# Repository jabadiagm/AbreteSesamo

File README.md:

# Ábrete Sésamo
Detector de proximidad / apertura de puertas por bluetooth

Ábrete Sésamo es un detector de proximidad basado en bluetooth que permite abrir la puerta de un hogar o de un garaje al detectar un dispositivo bluetooth dentro de un rango de 10m, aproximadamente. La centralita está formada por un arduino mega y una placa auxiliar. La placa contiene un relé para conectar al circuito de apertura y tres chips de bluetooth (2xHC05 + BLE112). El primer HC05 sirve para detectar teléfonos anteriores a los smartphones. El segundo HC05 detecta smartphones con bluetooth 1-3. Y el BLE112 sirve para smartphones con bluetooth 4. Los smartphones deben incluir una aplicación que se comunique con la centralita.

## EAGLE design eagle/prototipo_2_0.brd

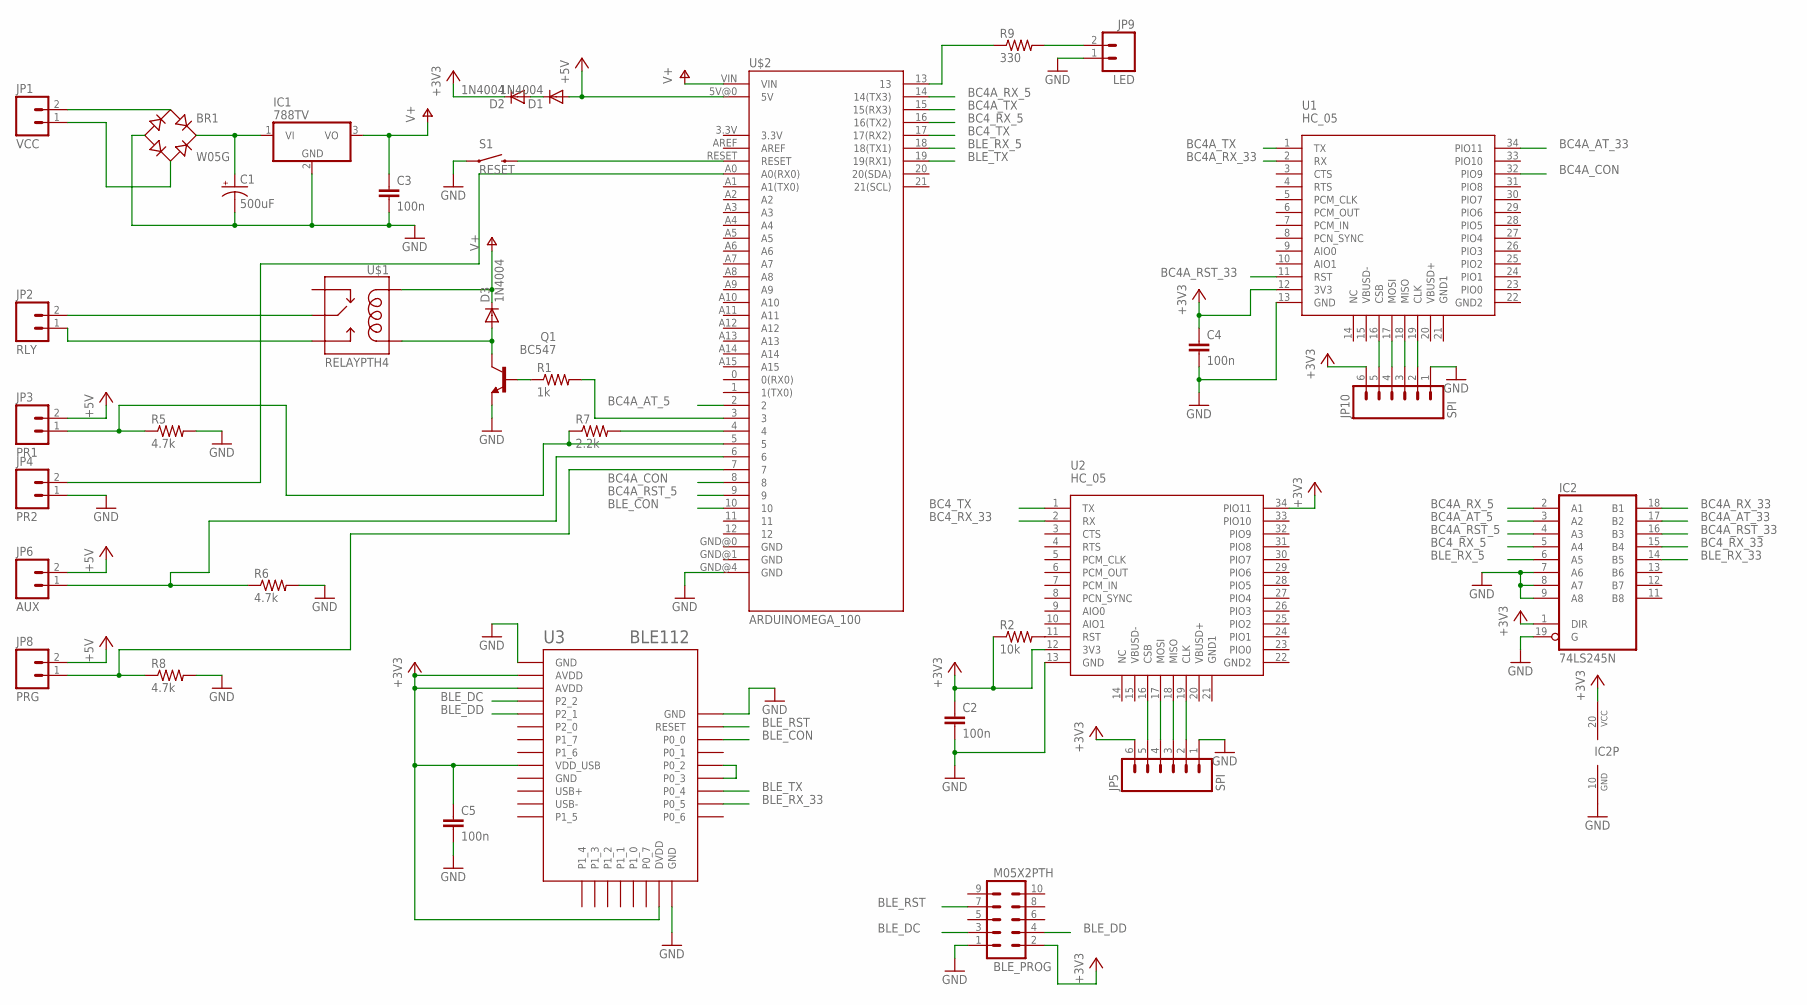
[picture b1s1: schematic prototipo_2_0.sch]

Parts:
BLE_PROG: M05X2PTH; AVR_ICSP
BR1: W05G; WOG
C1: 500uF; CPOL-RADIAL-1000UF-25V
C2, C3, C4, C5: 100n; C5B3
D1, D2, D3: 1N4004; DO41-10
IC1: 788TV; TO220V
IC2: 74LS245N; DIL20
JP1: VCC; SCREWTERMINAL-3.5MM-2
JP2: RLY; SCREWTERMINAL-3.5MM-2
JP3: PR1; SCREWTERMINAL-3.5MM-2
JP4: PR2; SCREWTERMINAL-3.5MM-2
JP5, JP10: SPI; 1X06
JP6: AUX; SCREWTERMINAL-3.5MM-2
JP8: PRG; SCREWTERMINAL-3.5MM-2
JP9: LED; SCREWTERMINAL-3.5MM-2
Q1: BC547; TO92
R1: 1k; AXIAL-0.4
R2: 10k; AXIAL-0.4
R5, R6, R8: 4.7k; AXIAL-0.4
R7: 2.2k; AXIAL-0.4
R9: 330; AXIAL-0.4
S1: RESET; TACTILE_SWITCH_SMD
U1, U2: HC_05; BLUETOOTH_SMD
U3: BLE112; BLE112-A
U$1: RELAYPTH4; RELAY-JZC
U$2: ARDUINOMEGA_100

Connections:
+3V3: BLE_PROG.2, C2.1, C4.1, C5.1, D2.C, IC2.1 (DIR), IC2.20 (VCC), JP5.6, JP10.6, R2.P$1 (1), U1.12 (3V3), U2.12 (3V3), U2.34 (PIO11), U3.AVDD1 (AVDD), U3.AVDD2 (AVDD), U3.DVDD, U3.VDD_USB
+5V: D1.A, JP3.2, JP6.2, JP8.2, U$2.5V@0 (5V)
BC4A_AT_5: IC2.3 (A2), U$2.2
BC4A_AT_33: IC2.17 (B2), U1.34 (PIO11)
BC4A_CON: U1.32 (PIO9), U$2.8
BC4A_RST_5: IC2.4 (A3), U$2.9
BC4A_RST_33: IC2.16 (B3), U1.11 (RST)
BC4A_RX_5: IC2.2 (A1), U$2.14 (14(TX3))
BC4A_RX_33: IC2.18 (B1), U1.2 (RX)
BC4A_TX: U1.1 (TX), U$2.15 (15(RX3))
BC4_RX_5: IC2.5 (A4), U$2.16 (16(TX2))
BC4_RX_33: IC2.15 (B4), U2.2 (RX)
BC4_TX: U2.1 (TX), U$2.17 (17(RX2))
BLE_CON: U3.P0_0, U$2.10
BLE_DC: BLE_PROG.3, U3.P2_2
BLE_DD: BLE_PROG.4, U3.P2_1
BLE_RST: BLE_PROG.7, U3.RESET
BLE_RX_5: IC2.6 (A5), U$2.18 (18(TX1))
BLE_RX_33: IC2.14 (B5), U3.P0_5
BLE_TX: U3.P0_4, U$2.19 (19(RX1))
GND: BLE_PROG.1, BR1.-, C1.2 (-), C2.2, C3.2, C4.2, C5.2, IC1.2 (GND), IC2.7 (A6), IC2.8 (A7), IC2.9 (A8), IC2.10 (GND), IC2.19 (G), JP4.1, JP5.1, JP9.1, JP10.1, Q1.1 (E), R5.P$2 (2), R6.P$2 (2), R8.P$2 (2), S1.1, U1.13 (GND), U2.13 (GND), U3.GND1 (GND), U3.GND2 (GND), U3.GND3 (GND), U3.GND4 (GND), U$2.GND@4 (GND)
unnamed: R2.P$2 (2), U2.11 (RST)
unnamed: D1.C, D2.A
unnamed: BR1.+, C1.1 (+), IC1.1 (VI)
unnamed: R1.P$2 (2), U$2.3
unnamed: Q1.2 (B), R1.P$1 (1)
unnamed: D3.A, Q1.3 (C), U$1.1 (COIL2)
unnamed: JP2.1, U$1.3 (NO)
unnamed: JP2.2, U$1.4 (MAIN)
unnamed: S1.3 (2), U$2.RESET
unnamed: U3.P0_2, U3.P0_3
unnamed: JP5.2, U2.19 (CLK)
unnamed: JP5.3, U2.18 (MISO)
unnamed: JP5.4, U2.17 (MOSI)
unnamed: JP5.5, U2.16 (CSB)
unnamed: JP10.5, U1.16 (CSB)
unnamed: JP3.1, R5.P$1 (1), R7.P$1 (1), U$2.5
unnamed: JP6.1, R6.P$1 (1), U$2.6
unnamed: R7.P$2 (2), U$2.4
unnamed: JP8.1, R8.P$1 (1), U$2.7
unnamed: JP10.4, U1.17 (MOSI)
unnamed: R9.P$1 (1), U$2.13
unnamed: JP9.2, R9.P$2 (2)
unnamed: JP10.3, U1.18 (MISO)
unnamed: JP10.2, U1.19 (CLK)
unnamed: JP4.2, U$2.A0 (A0(RX0))
V+: C3.1, D3.C, IC1.3 (VO), U$1.5 (COIL1), U$2.VIN
VCC1: BR1.AC1, JP1.2
VCC2: BR1.AC2, JP1.1

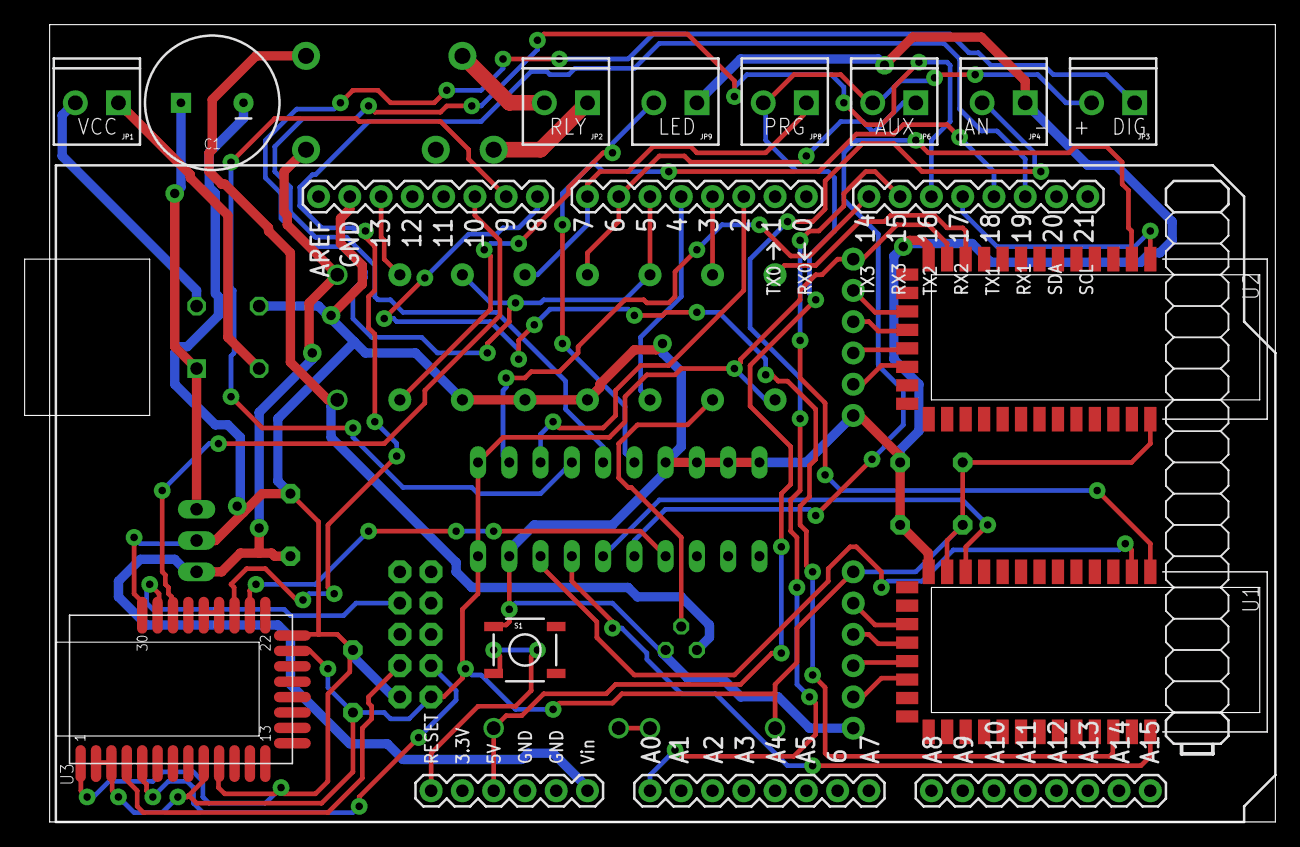
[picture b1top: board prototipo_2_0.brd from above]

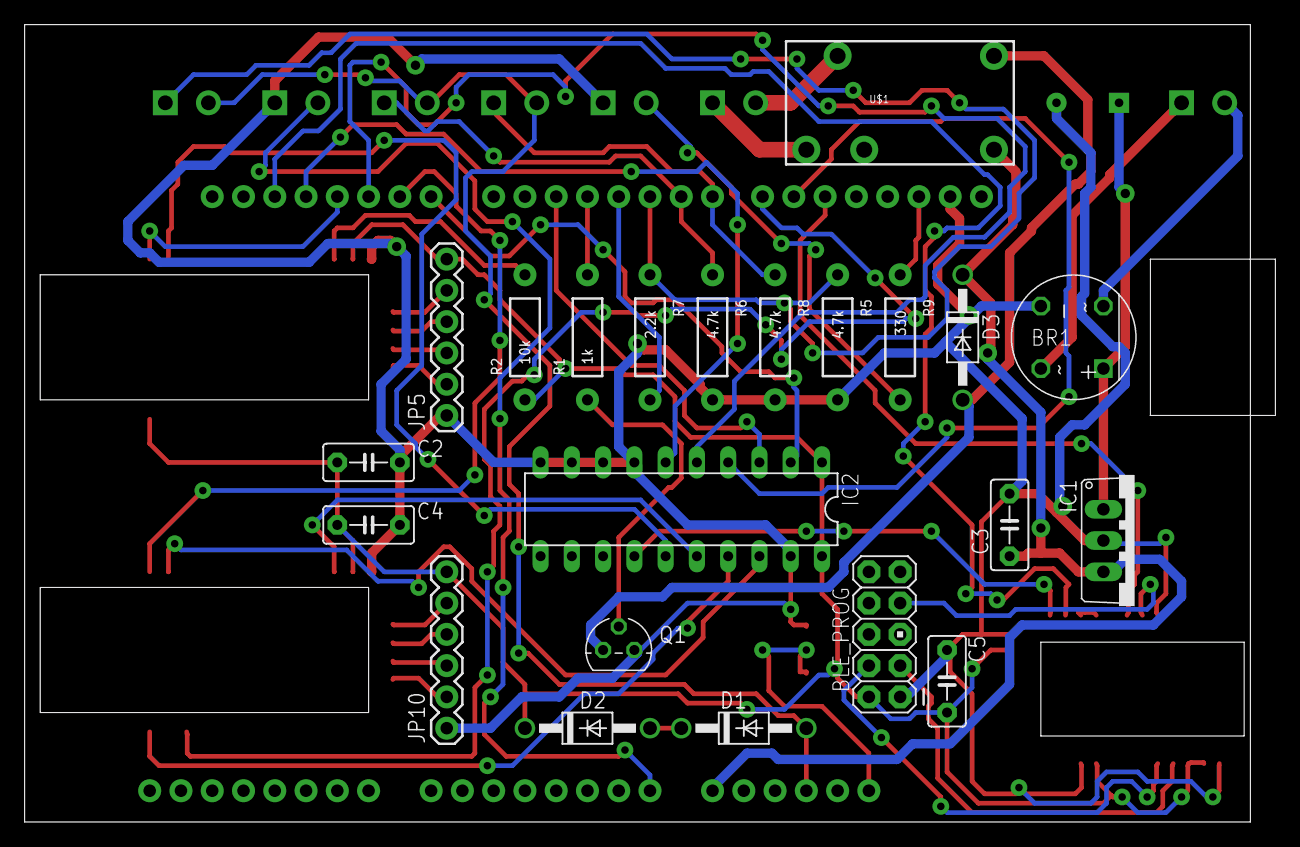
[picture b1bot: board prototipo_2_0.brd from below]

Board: 2 copper layers, 101.6 x 64.8 mm, 35 parts (22 on the bottom side), 49 nets.

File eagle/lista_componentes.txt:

Partlist

Exported from prototipo_2_0.sch at 14/11/2012 22:06:32

EAGLE Version 6.1.0 Copyright (c) 1988-2012 CadSoft

Assembly variant: 

Part     Value           Device                Package                Library                    Sheet

BLE_PROG M05X2PTH        M05X2PTH              AVR_ICSP               SparkFun-Connectors        1
BR1      W05G            W05G                  WOG                    dbridge                    1
C1       500uF           CAP_POLPTH4           CPOL-RADIAL-1000UF-25V SparkFun-Passives          1
C2       100n            C5/3                  C5B3                   capacitor-wima             1
C3       100n            C5/3                  C5B3                   capacitor-wima             1
C4       100n            C5/3                  C5B3                   capacitor-wima             1
C5       100n            C5/3                  C5B3                   capacitor-wima             1
D1       1N4004          1N4004                DO41-10                diode                      1
D2       1N4004          1N4004                DO41-10                diode                      1
D3       1N4004          1N4004                DO41-10                diode                      1
IC1      788TV           788TV                 TO220V                 linear                     1
IC2      74LS245N        74LS245N              DIL20                  adafruit                   1
JP1      VCC             M023.5MM              SCREWTERMINAL-3.5MM-2  SparkFun-Connectors        1
JP2      RLY             M023.5MM              SCREWTERMINAL-3.5MM-2  SparkFun-Connectors        1
JP3      PR1             M023.5MM              SCREWTERMINAL-3.5MM-2  SparkFun-Connectors        1
JP4      PR2             M023.5MM              SCREWTERMINAL-3.5MM-2  SparkFun-Connectors        1
JP5      SPI             M06SIP                1X06                   SparkFun-Connectors        1
JP6      AUX             M023.5MM              SCREWTERMINAL-3.5MM-2  SparkFun-Connectors        1
JP8      PRG             M023.5MM              SCREWTERMINAL-3.5MM-2  SparkFun-Connectors        1
JP9      LED             M023.5MM              SCREWTERMINAL-3.5MM-2  SparkFun-Connectors        1
JP10     SPI             M06SIP                1X06                   SparkFun-Connectors        1
Q1       BC547           BC547                 TO92                   transistor-npn             1
R1       1k              RESISTORPTH-1/4W      AXIAL-0.4              SparkFun-Passives          1
R2       10k             RESISTORPTH-1/4W      AXIAL-0.4              SparkFun-Passives          1
R5       4.7k            RESISTORPTH-1/4W      AXIAL-0.4              SparkFun-Passives          1
R6       4.7k            RESISTORPTH-1/4W      AXIAL-0.4              SparkFun-Passives          1
R7       2.2k            RESISTORPTH-1/4W      AXIAL-0.4              SparkFun-Passives          1
R8       4.7k            RESISTORPTH-1/4W      AXIAL-0.4              SparkFun-Passives          1
R9       330             RESISTORPTH-1/4W      AXIAL-0.4              SparkFun-Passives          1
S1       RESET           SWITCH-MOMENTARY-2SMD TACTILE_SWITCH_SMD     SparkFun-Electromechanical 1
U$1      RELAYPTH4       RELAYPTH4             RELAY-JZC              SparkFun-Electromechanical 1
U$2      ARDUINOMEGA_100 ARDUINOMEGA_100       ARDUINOMEGA_100        prymia                     1
U1       HC_05           HC_05                 BLUETOOTH_SMD          SerialPortBluetooth        1
U2       HC_05           HC_05                 BLUETOOTH_SMD          SerialPortBluetooth        1
U3       BLE112          BLE112-A-VISUAL       BLE112-A               sf-bluegiga                1

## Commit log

2020-06-07 Prototipo 2

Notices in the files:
parts and their libraries:
SparkFun-Connectors: Licensing: CC v3.0 Share-Alike You are welcome to use this library for commercial purposes.
